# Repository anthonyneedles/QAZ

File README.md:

# **QAZ**

## Table of Contents

1. [Boards](#boards)
1. [About This Project](#about-this-project)
    1. [File Structure](#file-structure)
    1. [Dependencies](#dependencies)
1. [Programming](#programming)
1. [Software](#software)
1. [Building](#building)

## **Boards**

### [**QAZ 65%**](docs/guides/QAZ_65.md)

### [**QAZ Media**](docs/guides/QAZ_Media.md)

## **About This Project**

The QAZ project was created as a way for me to learn the USB protocol by writing a bare-metal USB
driver. Since a keyboard is a relatively simple USB device, and I like mechanical keyboards, I
decided that it would be a perfect project. The QAZ project is planned to support various different
keyboard layouts (only 65% and a Media board for now).

This repository holds files for both the software and hardware portions of this project. The
software consists of C++ source and header files, built using Make. Building is only supported
in Debian-based systems. CMSIS is used for some MCU hardware abstraction.

The PCB(s) for the different board versions have their schematic and layouts designed in KiCad,
which are contained in this library and can be manufactured in any generic fabrication house.

There is a maker space at my work that has a laser cutter that can cut acrylic, so decided to try
to keep costs down and make a "sandwich" case, which consists of several stacked layers of acrylic.

### **File Structure**

```
└── QAZ/
    ├── build/
    │   └── CMake build directory
    │
    ├── docs/
    │   │── guides/
    │   │   └── board-specific info, software info, etc.
    │   │
    │   ├── doxygen/
    │   │   └── Doxygen html output
    │   │
    │   └── media/
    │       └── diagrams, pictures, etc.
    │
    ├── hardware/
    │   ├── common/
    │   │   └── hardware utility used by both (e.g. KiCad libraries)
    │   │
    │   └── QAZ_*/
    │       └── PCB/case layer subdirectories for each QAZ configuration
    │
    ├── scripts/
    │   └── useful project scripts (cpplint.py, Doxyfile, etc.)
    │
    ├── src/
    │   └── all source files/module subdirectories, source-level CMakeLists.txt
    │
    └── LICENSE, README, top-level Makefile/CMakeLists.txt
```

The `docs\doxygen` and `build` directories are not tracked, and get made when the project is built.
The files in these directories are removed when the project is cleaned with `make clean`.

## **Programming**

The board programming guide can be found at [`docs/guides/Programming.md`](docs/guides/Programming.md).

## **Software**

The software guide can be found at [`docs/guides/Software.md`](docs/guides/Software.md).

## **Building**

The software building guide can be found at [`docs/guides/Building.md`](docs/guides/Building.md).

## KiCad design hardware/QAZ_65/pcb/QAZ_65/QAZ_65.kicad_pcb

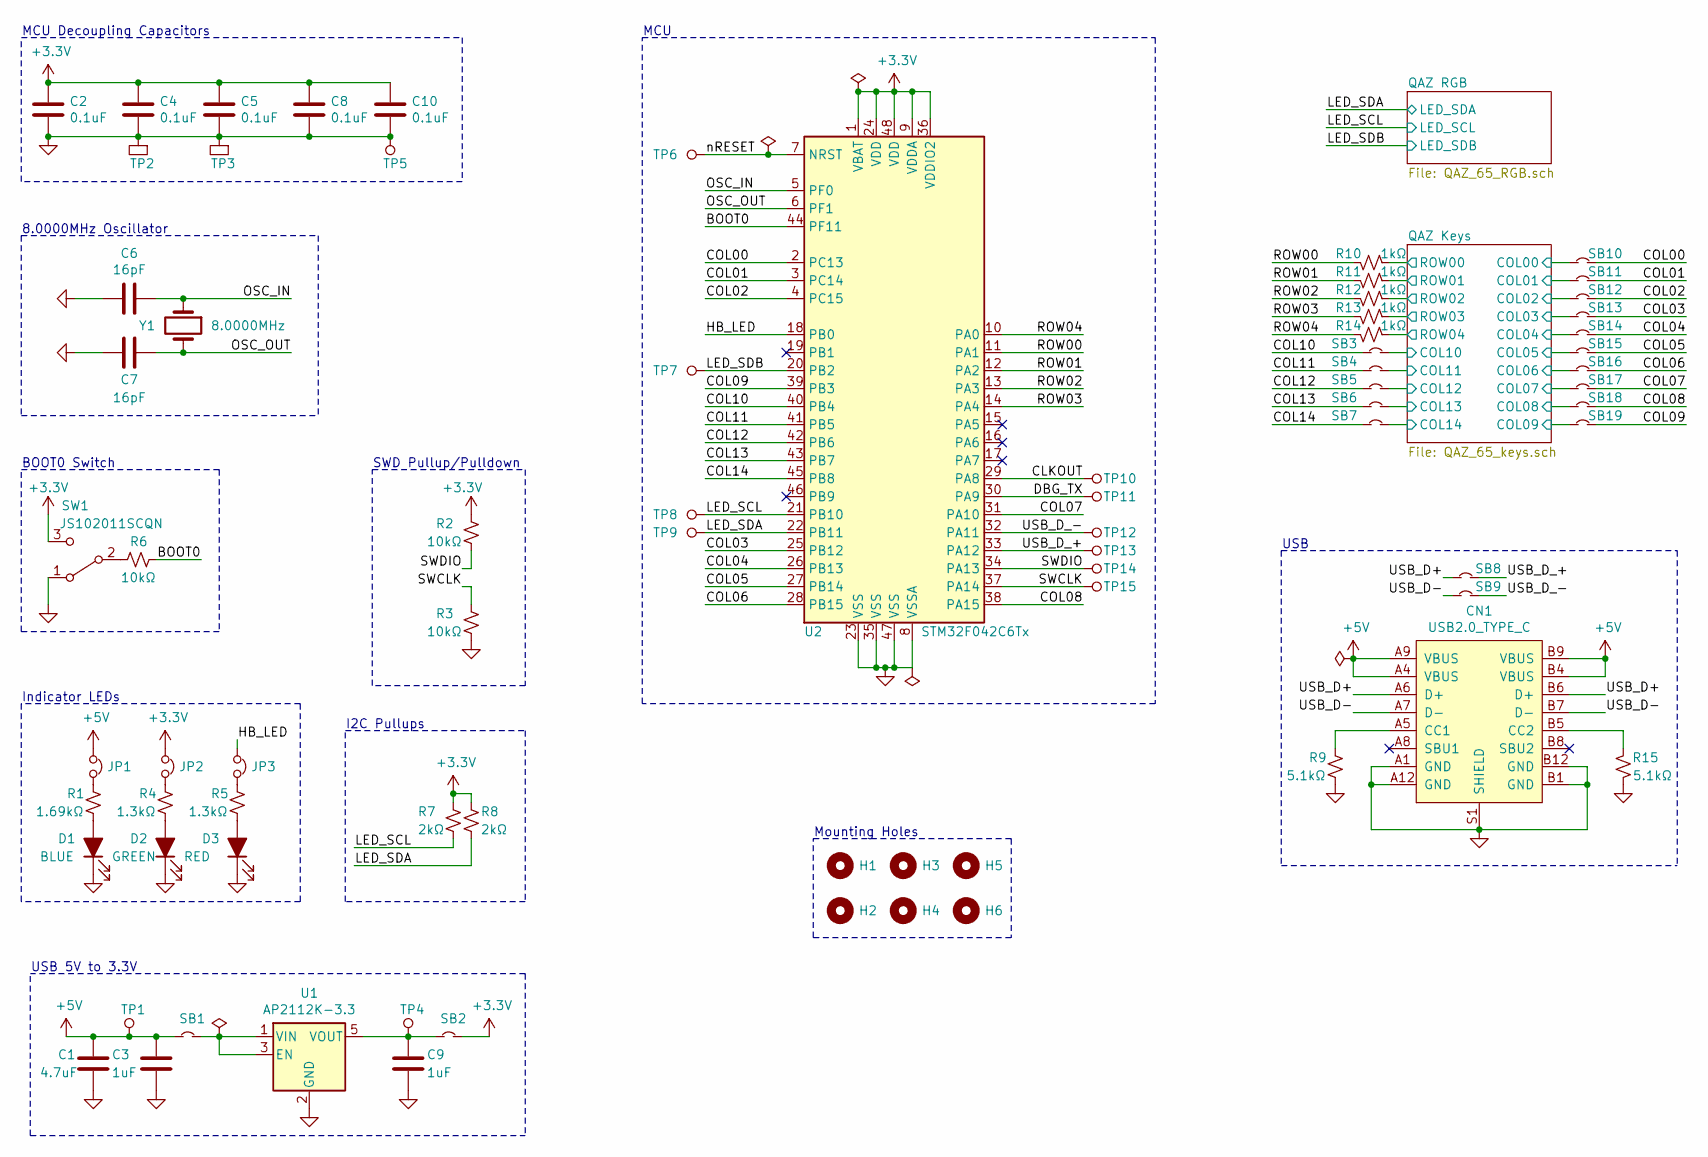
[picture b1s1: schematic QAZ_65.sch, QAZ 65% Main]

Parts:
C1: 4.7uF; C_0805_2012Metric_Pad1.15x1.40mm_HandSolder
C2, C4, C5, C8, C10: 0.1uF; C_0603_1608Metric_Pad1.05x0.95mm_HandSolder
C3, C9: 1uF; C_0603_1608Metric_Pad1.05x0.95mm_HandSolder
C6, C7: 16pF; C_0603_1608Metric_Pad1.05x0.95mm_HandSolder
CN1: USB2.0_TYPE_C; USB_C_GCT_USB4085
D1: BLUE; R_0603_1608Metric_Pad1.05x0.95mm_HandSolder
D2: GREEN; R_0603_1608Metric_Pad1.05x0.95mm_HandSolder
D3: RED; R_0603_1608Metric_Pad1.05x0.95mm_HandSolder
H1, H2, H3, H4, H5, H6: MountingHole; 4-40_NPTH
JP1, JP2, JP3: Jumper_NC_Small; PinHeader_1x02_P1.27mm_Vertical
R1: 1.69kΩ; R_0603_1608Metric_Pad1.05x0.95mm_HandSolder
R2, R3, R6: 10kΩ; R_0603_1608Metric_Pad1.05x0.95mm_HandSolder
R4, R5: 1.3kΩ; R_0603_1608Metric_Pad1.05x0.95mm_HandSolder
R7, R8: 2kΩ; R_0603_1608Metric_Pad1.05x0.95mm_HandSolder
R9, R15: 5.1kΩ; R_0603_1608Metric_Pad1.05x0.95mm_HandSolder
R10, R11, R12, R13, R14: 1kΩ; R_0603_1608Metric_Pad1.05x0.95mm_HandSolder
SB1, SB2, SB3, SB4, SB5, SB6, SB7, SB8, SB9, SB10, SB11, SB12, SB13, SB14, SB15, SB16, SB17, SB18, SB19: SolderBridge; R_0603_1608Metric_Pad1.05x0.95mm_HandSolder
SW1: JS102011SCQN; JS102011SCQN_SPDT
TP1, TP4, TP5, TP6, TP7, TP8, TP9, TP10, TP11, TP12, TP13, TP14, TP15: TestPoint; TestPoint_Thruhole_1.0mm
TP2, TP3: TestPoint_SMD_1812; TestPoint_SMD_1812_HS
U1: AP2112K-3.3; SOT-23-5
U2: STM32F042C6Tx; LQFP-48_7x7mm_P0.5mm
Y1: 8.0000MHz; Crystal_SMD_Abracon_ABM7-2Pin_6.0x3.5mm_HS

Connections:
+3V3: C2.2, C4.2, C5.2, C8.2, C10.2, JP2.1, R2.2, R7.2, R8.2, SB2.2, SW1.3 (C), U2.1 (VBAT), U2.9 (VDDA), U2.24 (VDD), U2.36 (VDDIO2), U2.48 (VDD); also elsewhere on the board
+5V: C1.2, C3.2, CN1.A4 (VBUS), CN1.A9 (VBUS), CN1.B4 (VBUS), CN1.B9 (VBUS), JP1.1, SB1.1, TP1.1; also elsewhere on the board
/BOOT0: R6.2, U2.44 (PF11)
/CLKOUT: TP10.1, U2.29 (PA8)
/COL00: SB10.2, U2.2 (PC13)
/COL01: SB11.2, U2.3 (PC14)
/COL02: SB12.2, U2.4 (PC15)
/COL03: SB13.2, U2.25 (PB12)
/COL04: SB14.2, U2.26 (PB13)
/COL05: SB15.2, U2.27 (PB14)
/COL06: SB16.2, U2.28 (PB15)
/COL07: SB17.2, U2.31 (PA10)
/COL08: SB18.2, U2.38 (PA15)
/COL09: SB19.2, U2.39 (PB3)
/COL10: SB3.1, U2.40 (PB4)
/COL11: SB4.1, U2.41 (PB5)
/COL12: SB5.1, U2.42 (PB6)
/COL13: SB6.1, U2.43 (PB7)
/COL14: SB7.1, U2.45 (PB8)
/DBG_TX: TP11.1, U2.30 (PA9)
/HB_LED: JP3.1, U2.18 (PB0)
/LED_SCL: R7.1, TP8.1, U2.21 (PB10); also elsewhere on the board
/LED_SDA: R8.1, TP9.1, U2.22 (PB11); also elsewhere on the board
/LED_SDB: TP7.1, U2.20 (PB2); also elsewhere on the board
/OSC_IN: C6.1, U2.5 (PF0), Y1.1
/OSC_OUT: C7.1, U2.6 (PF1), Y1.2
/QAZ Keys/COL00: SB10.1; also elsewhere on the board
/QAZ Keys/COL01: SB11.1; also elsewhere on the board
/QAZ Keys/COL02: SB12.1; also elsewhere on the board
/QAZ Keys/COL03: SB13.1; also elsewhere on the board
/QAZ Keys/COL04: SB14.1; also elsewhere on the board
/QAZ Keys/COL05: SB15.1; also elsewhere on the board
/QAZ Keys/COL06: SB16.1; also elsewhere on the board
/QAZ Keys/COL07: SB17.1; also elsewhere on the board
/QAZ Keys/COL08: SB18.1; also elsewhere on the board
/QAZ Keys/COL09: SB19.1; also elsewhere on the board
/QAZ Keys/COL10: SB3.2; also elsewhere on the board
/QAZ Keys/COL11: SB4.2; also elsewhere on the board
/QAZ Keys/COL12: SB5.2; also elsewhere on the board
/QAZ Keys/COL13: SB6.2; also elsewhere on the board
/QAZ Keys/COL14: SB7.2; also elsewhere on the board
/QAZ Keys/ROW00: R10.1; also elsewhere on the board
/QAZ Keys/ROW01: R11.1; also elsewhere on the board
/QAZ Keys/ROW02: R12.1; also elsewhere on the board
/QAZ Keys/ROW03: R13.1; also elsewhere on the board
/QAZ Keys/ROW04: R14.1; also elsewhere on the board
/ROW00: R10.2, U2.11 (PA1)
/ROW01: R11.2, U2.12 (PA2)
/ROW02: R12.2, U2.13 (PA3)
/ROW03: R13.2, U2.14 (PA4)
/ROW04: R14.2, U2.10 (PA0)
/SWCLK: R3.2, TP15.1, U2.37 (PA14)
/SWDIO: R2.1, TP14.1, U2.34 (PA13)
/USB_D+: CN1.A6 (D+), CN1.B6 (D+), SB8.1
/USB_D-: CN1.A7 (D-), CN1.B7 (D-), SB9.1
/USB_D_+: SB8.2, TP13.1, U2.33 (PA12)
/USB_D_-: SB9.2, TP12.1, U2.32 (PA11)
/nRESET: TP6.1, U2.7 (NRST)
GND: C1.1, C2.1, C3.1, C4.1, C5.1, C6.2, C7.2, C8.1, C9.1, C10.1, CN1.A1 (GND), CN1.A12 (GND), CN1.B1 (GND), CN1.B12 (GND), CN1.S1 (SHIELD), D1.1 (K), D2.1 (K), D3.1 (K), R3.1, R9.1, R15.1, SW1.1 (A), TP2.1, TP3.1, TP5.1, U1.2 (GND), U2.8 (VSSA), U2.23 (VSS), U2.35 (VSS), U2.47 (VSS); also elsewhere on the board
unnamed: C9.2, SB2.1, TP4.1, U1.5 (VOUT)
unnamed: CN1.A5 (CC1), R9.2
unnamed: CN1.B5 (CC2), R15.2
unnamed: D1.2 (A), R1.1
unnamed: D2.2 (A), R4.1
unnamed: D3.2 (A), R5.1
unnamed: JP1.2, R1.2
unnamed: JP2.2, R4.2
unnamed: JP3.2, R5.2
unnamed: R6.1, SW1.2 (B)
unnamed: SB1.2, U1.1 (VIN), U1.3 (EN)

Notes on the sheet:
USB 5V to 3.3V
MCU Decoupling Capacitors
8.0000MHz Oscillator
BOOT0 Switch
Indicator LEDs
I2C Pullups
MCU
SWD Pullup/Pulldown
USB
Mounting Holes

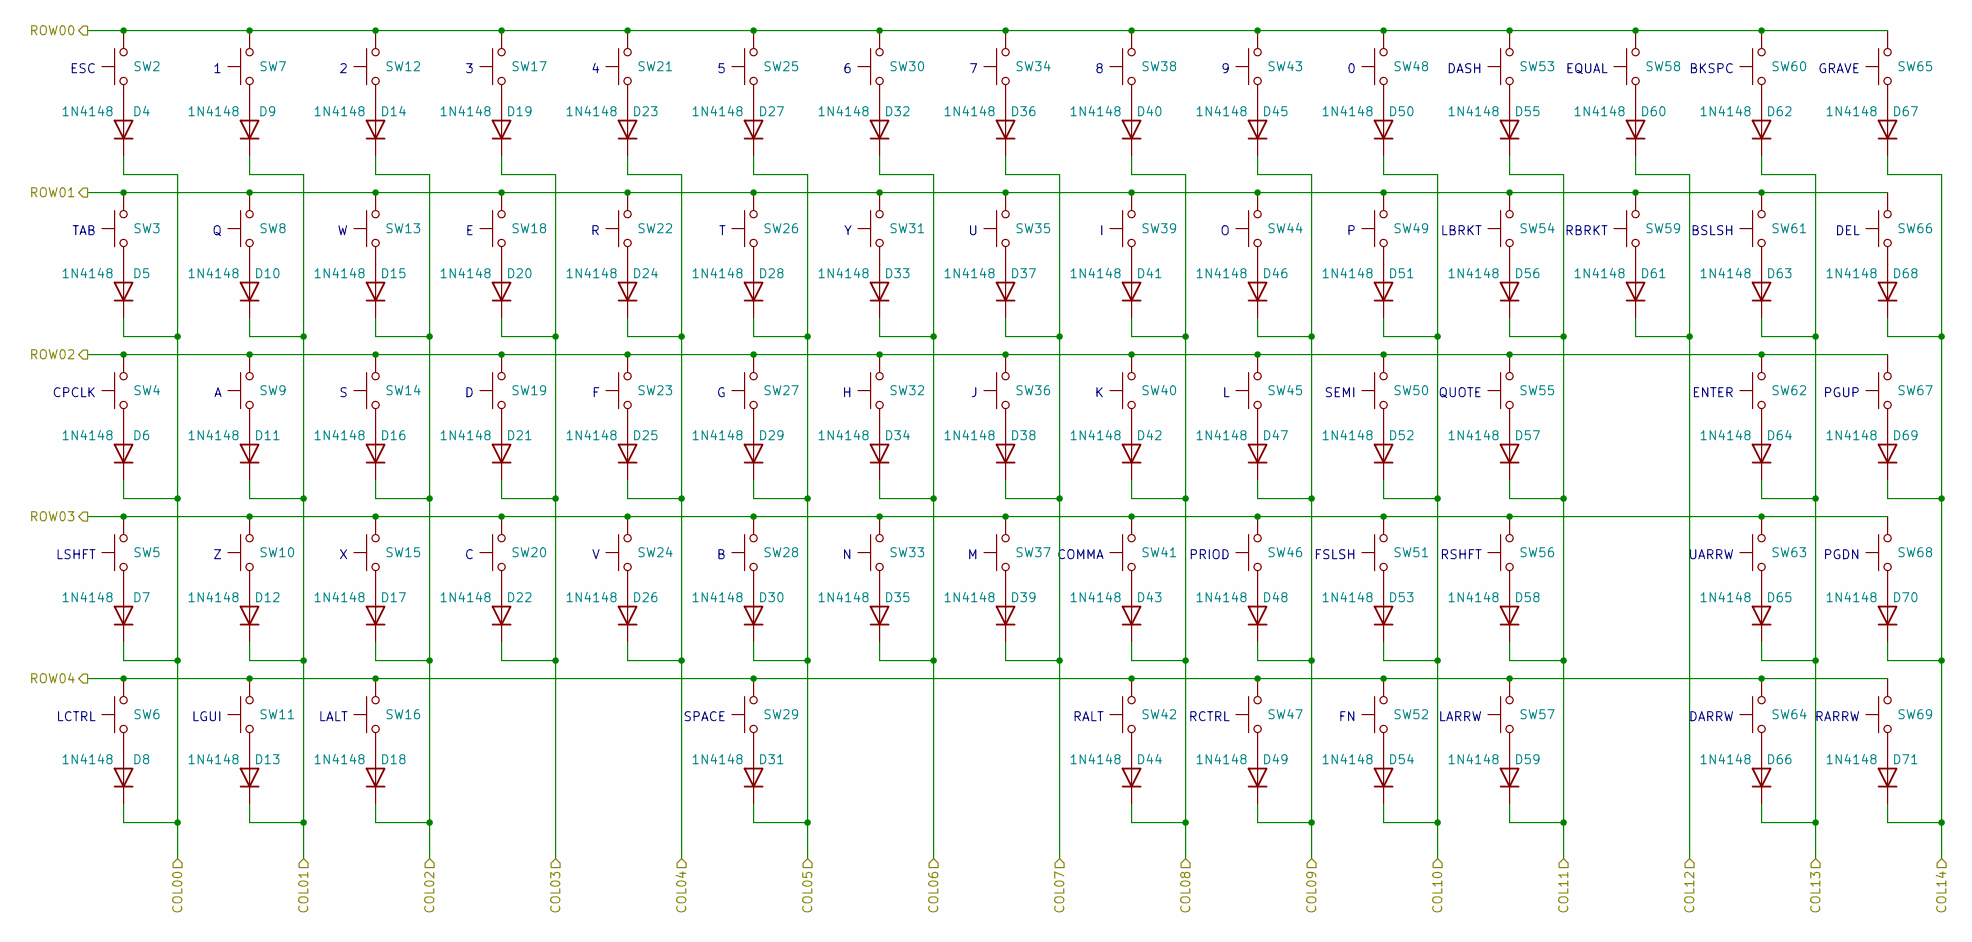
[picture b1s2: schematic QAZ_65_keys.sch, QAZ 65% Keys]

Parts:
D4, D5, D6, D7, D8, D9, D10, D11, D12, D13, D14, D15, D16, D17, D18, D19, D20, D21, D22, D23, D24, D25, D26, D27, D28, D29, D30, D31, D32, D33, D34, D35, D36, D37, D38, D39, D40, D41, D42, D43, D44, D45, D46, D47, D48, D49, D50, D51, D52, D53, D54, D55, D56, D57, D58, D59, D60, D61, D62, D63, D64, D65, D66, D67, D68, D69, D70, D71: 1N4148; D_DO-35_SOD27_P7.62mm_Horizontal
SW2, SW7, SW8, SW9, SW10, SW12, SW13, SW14, SW15, SW17, SW18, SW19, SW20, SW21, SW22, SW23, SW24, SW25, SW26, SW27, SW28, SW30, SW31, SW32, SW33, SW34, SW35, SW36, SW37, SW38, SW39, SW40, SW41, SW42, SW43, SW44, SW45, SW46, SW47, SW48, SW49, SW50, SW51, SW52, SW53, SW54, SW55, SW57, SW58, SW59, SW63, SW64, SW65, SW66, SW67, SW68, SW69: Cherry MX; SW_Cherry_MX_1.00u_PCB
SW3, SW61: Cherry MX; SW_Cherry_MX_1.50u_PCB
SW4, SW56: Cherry MX; SW_Cherry_MX_1.75u_PCB
SW5, SW62: Cherry MX; SW_Cherry_MX_2.25u_PCB
SW6, SW11, SW16: Cherry MX; SW_Cherry_MX_1.25u_PCB
SW29: Cherry MX; SW_Cherry_MX_6.25u_PCB
SW60: Cherry MX; SW_Cherry_MX_2.00u_PCB

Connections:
/QAZ Keys/COL00: D4.1 (K), D5.1 (K), D6.1 (K), D7.1 (K), D8.1 (K); also elsewhere on the board
/QAZ Keys/COL01: D9.1 (K), D10.1 (K), D11.1 (K), D12.1 (K), D13.1 (K); also elsewhere on the board
/QAZ Keys/COL02: D14.1 (K), D15.1 (K), D16.1 (K), D17.1 (K), D18.1 (K); also elsewhere on the board
/QAZ Keys/COL03: D19.1 (K), D20.1 (K), D21.1 (K), D22.1 (K); also elsewhere on the board
/QAZ Keys/COL04: D23.1 (K), D24.1 (K), D25.1 (K), D26.1 (K); also elsewhere on the board
/QAZ Keys/COL05: D27.1 (K), D28.1 (K), D29.1 (K), D30.1 (K), D31.1 (K); also elsewhere on the board
/QAZ Keys/COL06: D32.1 (K), D33.1 (K), D34.1 (K), D35.1 (K); also elsewhere on the board
/QAZ Keys/COL07: D36.1 (K), D37.1 (K), D38.1 (K), D39.1 (K); also elsewhere on the board
/QAZ Keys/COL08: D40.1 (K), D41.1 (K), D42.1 (K), D43.1 (K), D44.1 (K); also elsewhere on the board
/QAZ Keys/COL09: D45.1 (K), D46.1 (K), D47.1 (K), D48.1 (K), D49.1 (K); also elsewhere on the board
/QAZ Keys/COL10: D50.1 (K), D51.1 (K), D52.1 (K), D53.1 (K), D54.1 (K); also elsewhere on the board
/QAZ Keys/COL11: D55.1 (K), D56.1 (K), D57.1 (K), D58.1 (K), D59.1 (K); also elsewhere on the board
/QAZ Keys/COL12: D60.1 (K), D61.1 (K); also elsewhere on the board
/QAZ Keys/COL13: D62.1 (K), D63.1 (K), D64.1 (K), D65.1 (K), D66.1 (K); also elsewhere on the board
/QAZ Keys/COL14: D67.1 (K), D68.1 (K), D69.1 (K), D70.1 (K), D71.1 (K); also elsewhere on the board
/QAZ Keys/ROW00: SW2.2, SW7.2, SW12.2, SW17.2, SW21.2, SW25.2, SW30.2, SW34.2, SW38.2, SW43.2, SW48.2, SW53.2, SW58.2, SW60.2, SW65.2; also elsewhere on the board
/QAZ Keys/ROW01: SW3.2, SW8.2, SW13.2, SW18.2, SW22.2, SW26.2, SW31.2, SW35.2, SW39.2, SW44.2, SW49.2, SW54.2, SW59.2, SW61.2, SW66.2; also elsewhere on the board
/QAZ Keys/ROW02: SW4.2, SW9.2, SW14.2, SW19.2, SW23.2, SW27.2, SW32.2, SW36.2, SW40.2, SW45.2, SW50.2, SW55.2, SW62.2, SW67.2; also elsewhere on the board
/QAZ Keys/ROW03: SW5.2, SW10.2, SW15.2, SW20.2, SW24.2, SW28.2, SW33.2, SW37.2, SW41.2, SW46.2, SW51.2, SW56.2, SW63.2, SW68.2; also elsewhere on the board
/QAZ Keys/ROW04: SW6.2, SW11.2, SW16.2, SW29.2, SW42.2, SW47.2, SW52.2, SW57.2, SW64.2, SW69.2; also elsewhere on the board
unnamed: D4.2 (A), SW2.1
unnamed: D5.2 (A), SW3.1
unnamed: D6.2 (A), SW4.1
unnamed: D7.2 (A), SW5.1
unnamed: D8.2 (A), SW6.1
unnamed: D9.2 (A), SW7.1
unnamed: D10.2 (A), SW8.1
unnamed: D11.2 (A), SW9.1
unnamed: D12.2 (A), SW10.1
unnamed: D13.2 (A), SW11.1
unnamed: D14.2 (A), SW12.1
unnamed: D15.2 (A), SW13.1
unnamed: D16.2 (A), SW14.1
unnamed: D17.2 (A), SW15.1
unnamed: D18.2 (A), SW16.1
unnamed: D19.2 (A), SW17.1
unnamed: D20.2 (A), SW18.1
unnamed: D21.2 (A), SW19.1
unnamed: D22.2 (A), SW20.1
unnamed: D23.2 (A), SW21.1
unnamed: D24.2 (A), SW22.1
unnamed: D25.2 (A), SW23.1
unnamed: D26.2 (A), SW24.1
unnamed: D27.2 (A), SW25.1
unnamed: D28.2 (A), SW26.1
unnamed: D29.2 (A), SW27.1
unnamed: D30.2 (A), SW28.1
unnamed: D31.2 (A), SW29.1
unnamed: D32.2 (A), SW30.1
unnamed: D33.2 (A), SW31.1
unnamed: D34.2 (A), SW32.1
unnamed: D35.2 (A), SW33.1
unnamed: D36.2 (A), SW34.1
unnamed: D37.2 (A), SW35.1
unnamed: D38.2 (A), SW36.1
unnamed: D39.2 (A), SW37.1
unnamed: D40.2 (A), SW38.1
unnamed: D41.2 (A), SW39.1
unnamed: D42.2 (A), SW40.1
unnamed: D43.2 (A), SW41.1
unnamed: D44.2 (A), SW42.1
unnamed: D45.2 (A), SW43.1
unnamed: D46.2 (A), SW44.1
unnamed: D47.2 (A), SW45.1
unnamed: D48.2 (A), SW46.1
unnamed: D49.2 (A), SW47.1
unnamed: D50.2 (A), SW48.1
unnamed: D51.2 (A), SW49.1
unnamed: D52.2 (A), SW50.1
unnamed: D53.2 (A), SW51.1
unnamed: D54.2 (A), SW52.1
unnamed: D55.2 (A), SW53.1
unnamed: D56.2 (A), SW54.1
unnamed: D57.2 (A), SW55.1
unnamed: D58.2 (A), SW56.1
unnamed: D59.2 (A), SW57.1
unnamed: D60.2 (A), SW58.1
unnamed: D61.2 (A), SW59.1
unnamed: D62.2 (A), SW60.1
unnamed: D63.2 (A), SW61.1
unnamed: D64.2 (A), SW62.1
unnamed: D65.2 (A), SW63.1
unnamed: D66.2 (A), SW64.1
unnamed: D67.2 (A), SW65.1
unnamed: D68.2 (A), SW66.1
unnamed: D69.2 (A), SW67.1
unnamed: D70.2 (A), SW68.1
unnamed: D71.2 (A), SW69.1

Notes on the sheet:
LCTRL
ESC
TAB
CPCLK
LSHFT
DASH
EQUAL
BKSPC
GRAVE
LGUI
LALT
LBRKT
RBRKT
BSLSH
DEL
SEMI
QUOTE
ENTER
PGUP
COMMA
PRIOD
FSLSH
RCTRL
RSHFT
SPACE
RALT
LARRW
PGDN
RARRW
DARRW
UARRW

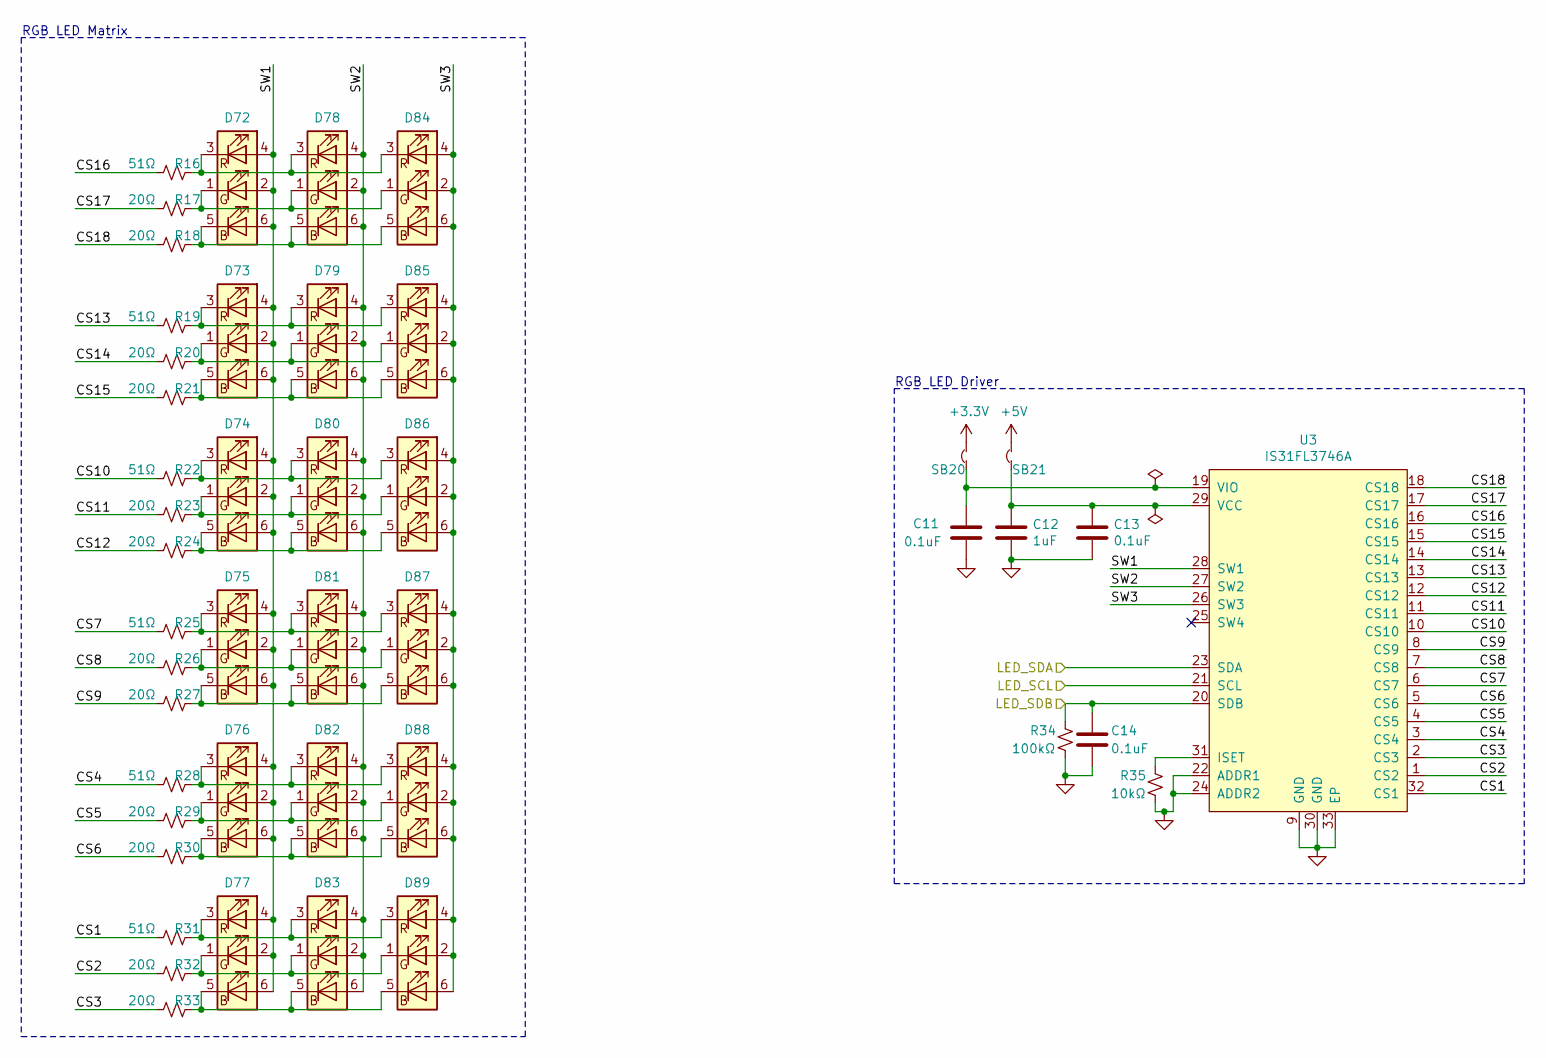
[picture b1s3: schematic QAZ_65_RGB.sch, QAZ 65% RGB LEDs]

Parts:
C11, C13, C14: 0.1uF; C_0603_1608Metric_Pad1.05x0.95mm_HandSolder
C12: 1uF; C_0603_1608Metric_Pad1.05x0.95mm_HandSolder
D72, D73, D74, D75, D76, D77, D78, D79, D80, D81, D82, D83, D84, D85, D86, D87, D88, D89: 19-337C_RSBHGHC-A88_4T; 0606_1616Metric_HS
R16, R19, R22, R25, R28, R31: 51Ω; R_0603_1608Metric_Pad1.05x0.95mm_HandSolder
R17, R18, R20, R21, R23, R24, R26, R27, R29, R30, R32, R33: 20Ω; R_0603_1608Metric_Pad1.05x0.95mm_HandSolder
R34: 100kΩ; R_0603_1608Metric_Pad1.05x0.95mm_HandSolder
R35: 10kΩ; R_0603_1608Metric_Pad1.05x0.95mm_HandSolder
SB20, SB21: SolderBridge; R_0603_1608Metric_Pad1.05x0.95mm_HandSolder
U3: IS31FL3746A; QFN-32-1EP_4x4mm_P0.4mm_EP2.9x2.9mm_HS

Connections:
+3V3: SB20.2; also elsewhere on the board
+5V: SB21.2; also elsewhere on the board
/LED_SCL: U3.21 (SCL); also elsewhere on the board
/LED_SDA: U3.23 (SDA); also elsewhere on the board
/LED_SDB: C14.2, R34.2, U3.20 (SDB); also elsewhere on the board
/QAZ RGB/CS1: R31.2, U3.32 (CS1)
/QAZ RGB/CS2: R32.2, U3.1 (CS2)
/QAZ RGB/CS3: R33.2, U3.2 (CS3)
/QAZ RGB/CS4: R28.2, U3.3 (CS4)
/QAZ RGB/CS5: R29.2, U3.4 (CS5)
/QAZ RGB/CS6: R30.2, U3.5 (CS6)
/QAZ RGB/CS7: R25.2, U3.6 (CS7)
/QAZ RGB/CS8: R26.2, U3.7 (CS8)
/QAZ RGB/CS9: R27.2, U3.8 (CS9)
/QAZ RGB/CS10: R22.2, U3.10 (CS10)
/QAZ RGB/CS11: R23.2, U3.11 (CS11)
/QAZ RGB/CS12: R24.2, U3.12 (CS12)
/QAZ RGB/CS13: R19.2, U3.13 (CS13)
/QAZ RGB/CS14: R20.2, U3.14 (CS14)
/QAZ RGB/CS15: R21.2, U3.15 (CS15)
/QAZ RGB/CS16: R16.2, U3.16 (CS16)
/QAZ RGB/CS17: R17.2, U3.17 (CS17)
/QAZ RGB/CS18: R18.2, U3.18 (CS18)
/QAZ RGB/SW1: D72.2, D72.4, D72.6, D73.2, D73.4, D73.6, D74.2, D74.4, D74.6, D75.2, D75.4, D75.6, D76.2, D76.4, D76.6, D77.2, D77.4, D77.6, U3.28 (SW1)
/QAZ RGB/SW2: D78.2, D78.4, D78.6, D79.2, D79.4, D79.6, D80.2, D80.4, D80.6, D81.2, D81.4, D81.6, D82.2, D82.4, D82.6, D83.2, D83.4, D83.6, U3.27 (SW2)
/QAZ RGB/SW3: D84.2, D84.4, D84.6, D85.2, D85.4, D85.6, D86.2, D86.4, D86.6, D87.2, D87.4, D87.6, D88.2, D88.4, D88.6, D89.2, D89.4, D89.6, U3.26 (SW3)
GND: C11.1, C12.1, C13.1, C14.1, R34.1, R35.1, U3.9 (GND), U3.22 (ADDR1), U3.24 (ADDR2), U3.30 (GND), U3.33 (EP); also elsewhere on the board
unnamed: C11.2, SB20.1, U3.19 (VIO)
unnamed: C12.2, C13.2, SB21.1, U3.29 (VCC)
unnamed: D72.1, D78.1, D84.1, R17.1
unnamed: D72.3, D78.3, D84.3, R16.1
unnamed: D72.5, D78.5, D84.5, R18.1
unnamed: D73.1, D79.1, D85.1, R20.1
unnamed: D73.3, D79.3, D85.3, R19.1
unnamed: D73.5, D79.5, D85.5, R21.1
unnamed: D74.1, D80.1, D86.1, R23.1
unnamed: D74.3, D80.3, D86.3, R22.1
unnamed: D74.5, D80.5, D86.5, R24.1
unnamed: D75.1, D81.1, D87.1, R26.1
unnamed: D75.3, D81.3, D87.3, R25.1
unnamed: D75.5, D81.5, D87.5, R27.1
unnamed: D76.1, D82.1, D88.1, R29.1
unnamed: D76.3, D82.3, D88.3, R28.1
unnamed: D76.5, D82.5, D88.5, R30.1
unnamed: D77.1, D83.1, D89.1, R32.1
unnamed: D77.3, D83.3, D89.3, R31.1
unnamed: D77.5, D83.5, D89.5, R33.1
unnamed: R35.2, U3.31 (ISET)

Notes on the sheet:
RGB LED Driver
RGB LED Matrix

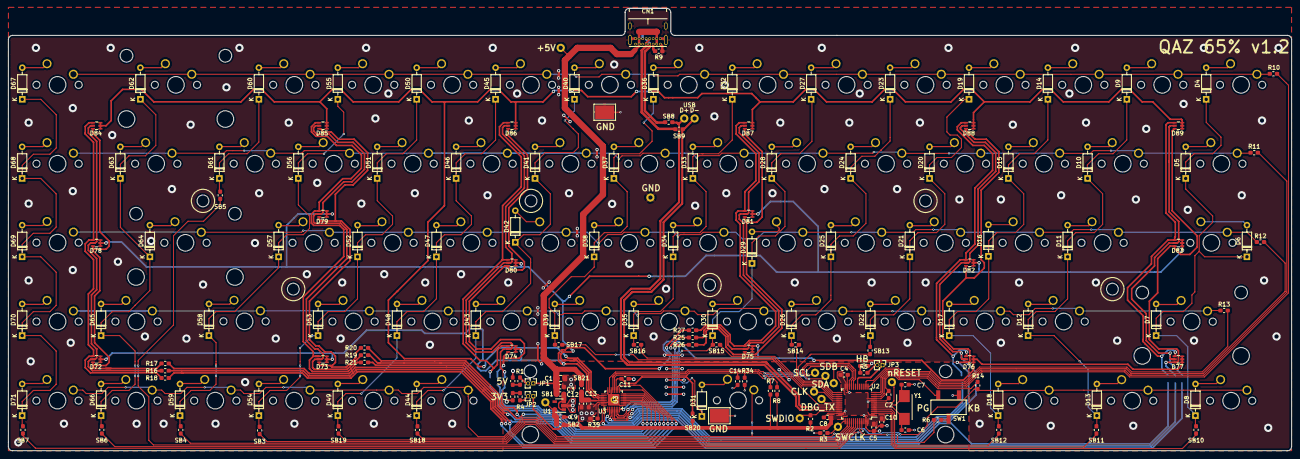
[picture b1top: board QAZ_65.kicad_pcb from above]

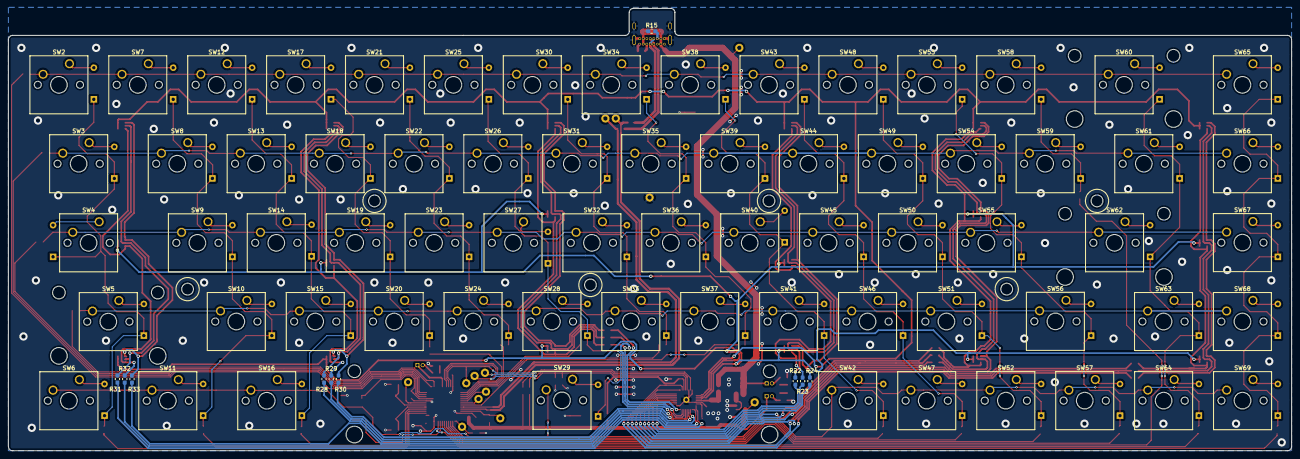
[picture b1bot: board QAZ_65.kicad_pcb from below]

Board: 2 copper layers, 309.0 x 106.5 mm, 257 parts (78 on the bottom side), 180 nets.

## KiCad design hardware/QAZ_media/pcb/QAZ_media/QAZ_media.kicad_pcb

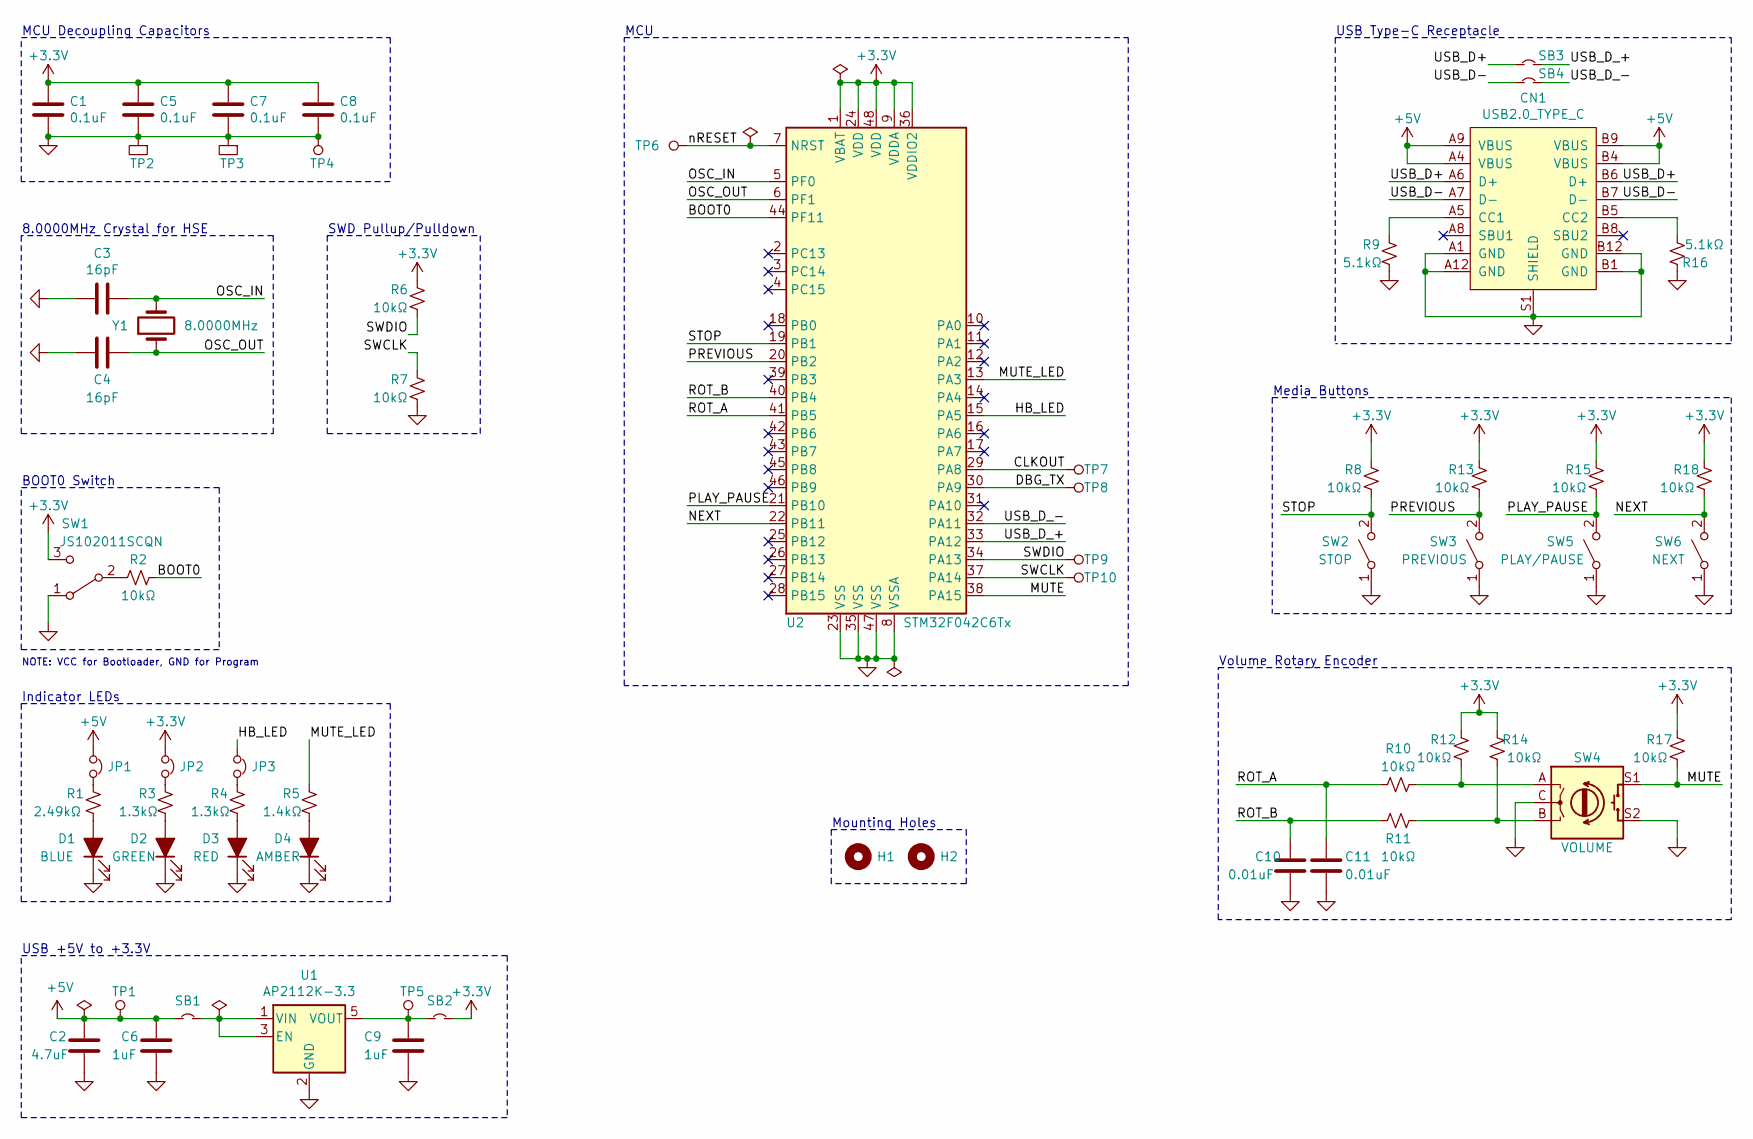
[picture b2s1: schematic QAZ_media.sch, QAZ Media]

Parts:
C1, C5, C7, C8: 0.1uF; C_0603_1608Metric_Pad1.05x0.95mm_HandSolder
C2: 4.7uF; C_0805_2012Metric_Pad1.15x1.40mm_HandSolder
C3, C4: 16pF; C_0603_1608Metric_Pad1.05x0.95mm_HandSolder
C6, C9: 1uF; C_0603_1608Metric_Pad1.05x0.95mm_HandSolder
C10, C11: 0.01uF; C_0603_1608Metric_Pad1.05x0.95mm_HandSolder
CN1: USB2.0_TYPE_C; USB_C_GCT_USB4085
D1: BLUE; R_0603_1608Metric_Pad1.05x0.95mm_HandSolder
D2: GREEN; R_0603_1608Metric_Pad1.05x0.95mm_HandSolder
D3: RED; R_0603_1608Metric_Pad1.05x0.95mm_HandSolder
D4: AMBER; PinHeader_1x02_P2.54mm_Vertical
H1, H2: MountingHole; 4-40_NPTH
JP1, JP2, JP3: Jumper_NC_Small; PinHeader_1x02_P1.27mm_Vertical
R1: 2.49kΩ; R_0603_1608Metric_Pad1.05x0.95mm_HandSolder
R2, R6, R7, R8, R10, R11, R12, R13, R14, R15, R17, R18: 10kΩ; R_0603_1608Metric_Pad1.05x0.95mm_HandSolder
R3, R4: 1.3kΩ; R_0603_1608Metric_Pad1.05x0.95mm_HandSolder
R5: 1.4kΩ; R_0603_1608Metric_Pad1.05x0.95mm_HandSolder
R9, R16: 5.1kΩ; R_0603_1608Metric_Pad1.05x0.95mm_HandSolder
SB1, SB2, SB3, SB4: SolderBridge; R_0603_1608Metric_Pad1.05x0.95mm_HandSolder
SW1: JS102011SCQN; JS102011SCQN_SPDT
SW2: STOP; NCA2
SW3: PREVIOUS; NCA2
SW4: VOLUME; RotaryEncoder_Alps_EC11E-Switch_Vertical_H20mm
SW5: PLAY/PAUSE; NCA2
SW6: NEXT; NCA2
TP1, TP4, TP5, TP6, TP7, TP8, TP9, TP10: TestPoint_Thruhole_0.7mm
TP2, TP3: TestPoint_SMD_1812; TestPoint_SMD_1812_HS
U1: AP2112K-3.3; SOT-23-5
U2: STM32F042C6Tx; LQFP-48_7x7mm_P0.5mm
Y1: 8.0000MHz; Crystal_SMD_Abracon_ABM7-2Pin_6.0x3.5mm_HS

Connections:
+3V3: C1.1, C5.1, C7.1, C8.1, JP2.1, R6.1, R8.1, R12.1, R13.1, R14.1, R15.1, R17.1, R18.1, SB2.2, SW1.3 (C), U2.1 (VBAT), U2.9 (VDDA), U2.24 (VDD), U2.36 (VDDIO2), U2.48 (VDD)
+5V: C2.1, C6.1, CN1.A4 (VBUS), CN1.A9 (VBUS), CN1.B4 (VBUS), CN1.B9 (VBUS), JP1.1, SB1.1, TP1.1
/BOOT0: R2.1, U2.44 (PF11)
/CLKOUT: TP7.1, U2.29 (PA8)
/DBG_TX: TP8.1, U2.30 (PA9)
/HB_LED: JP3.1, U2.15 (PA5)
/MUTE: R17.2, SW4.S1, U2.38 (PA15)
/MUTE_LED: R5.1, U2.13 (PA3)
/NEXT: R18.2, SW6.2 (B), U2.22 (PB11)
/OSC_IN: C3.1, U2.5 (PF0), Y1.2
/OSC_OUT: C4.1, U2.6 (PF1), Y1.1
/PLAY_PAUSE: R15.2, SW5.2 (B), U2.21 (PB10)
/PREVIOUS: R13.2, SW3.2 (B), U2.20 (PB2)
/ROT_A: C11.1, R10.1, U2.41 (PB5)
/ROT_B: C10.1, R11.1, U2.40 (PB4)
/STOP: R8.2, SW2.2 (B), U2.19 (PB1)
/SWCLK: R7.1, TP10.1, U2.37 (PA14)
/SWDIO: R6.2, TP9.1, U2.34 (PA13)
/USB_D+: CN1.A6 (D+), CN1.B6 (D+), SB3.1
/USB_D-: CN1.A7 (D-), CN1.B7 (D-), SB4.1
/USB_D_+: SB3.2, U2.33 (PA12)
/USB_D_-: SB4.2, U2.32 (PA11)
/nRESET: TP6.1, U2.7 (NRST)
GND: C1.2, C2.2, C3.2, C4.2, C5.2, C6.2, C7.2, C8.2, C9.2, C10.2, C11.2, CN1.A1 (GND), CN1.A12 (GND), CN1.B1 (GND), CN1.B12 (GND), CN1.S1 (SHIELD), D1.1 (K), D2.1 (K), D3.1 (K), D4.1 (K), R7.2, R9.2, R16.1, SW1.1 (A), SW2.1 (A), SW3.1 (A), SW4.C, SW4.S2, SW5.1 (A), SW6.1 (A), TP2.1, TP3.1, TP4.1, U1.2 (GND), U2.8 (VSSA), U2.23 (VSS), U2.35 (VSS), U2.47 (VSS)
unnamed: C9.1, SB2.1, TP5.1, U1.5 (VOUT)
unnamed: CN1.A5 (CC1), R9.1
unnamed: CN1.B5 (CC2), R16.2
unnamed: D1.2 (A), R1.2
unnamed: D2.2 (A), R3.2
unnamed: D3.2 (A), R4.2
unnamed: D4.2 (A), R5.2
unnamed: JP1.2, R1.1
unnamed: JP2.2, R3.1
unnamed: JP3.2, R4.1
unnamed: R2.2, SW1.2 (B)
unnamed: R10.2, R12.2, SW4.A
unnamed: R11.2, R14.2, SW4.B
unnamed: SB1.2, U1.1 (VIN), U1.3 (EN)

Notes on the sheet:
MCU Decoupling Capacitors
8.0000MHz Crystal for HSE
BOOT0 Switch
NOTE: VCC for Bootloader, GND for Program
Indicator LEDs
USB +5V to +3.3V
SWD Pullup/Pulldown
MCU
USB Type-C Receptacle
Media Buttons
Volume Rotary Encoder
Mounting Holes

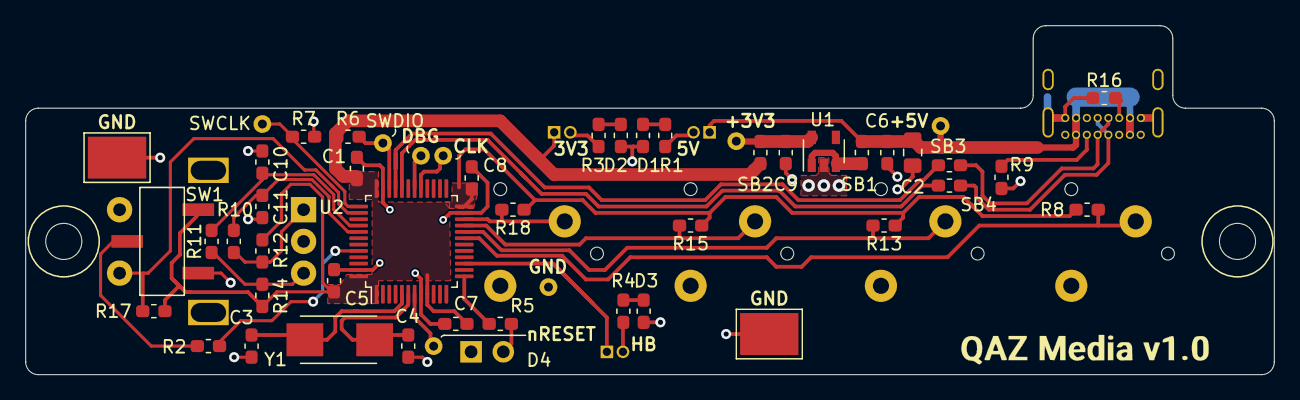
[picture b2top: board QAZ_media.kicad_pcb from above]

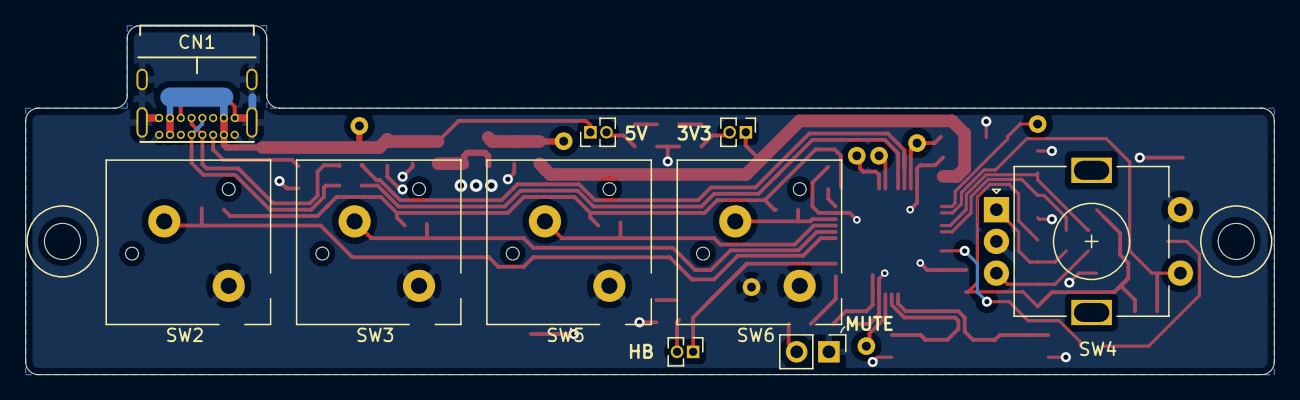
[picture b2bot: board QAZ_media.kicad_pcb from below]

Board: 2 copper layers, 98.4 x 27.5 mm, 62 parts (10 on the bottom side), 38 nets.

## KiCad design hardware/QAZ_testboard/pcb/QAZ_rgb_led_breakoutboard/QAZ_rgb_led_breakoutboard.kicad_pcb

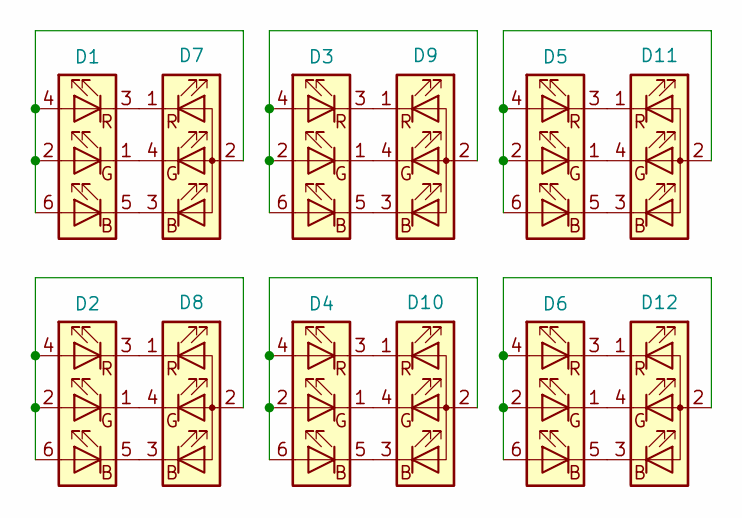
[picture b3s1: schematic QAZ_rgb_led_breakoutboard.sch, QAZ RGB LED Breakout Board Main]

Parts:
D1, D2, D3, D4, D5, D6: 19-337C_RSBHGHC-A88_4T; 0606_1616Metric_HS
D7, D8, D9, D10, D11, D12: LED_RABG; LED_D5.0mm-4_RGB

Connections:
unnamed: D1.1, D7.4 (GK)
unnamed: D1.2, D1.4, D1.6, D7.2 (A)
unnamed: D1.3, D7.1 (RK)
unnamed: D1.5, D7.3 (BK)
unnamed: D2.1, D8.4 (GK)
unnamed: D2.2, D2.4, D2.6, D8.2 (A)
unnamed: D2.3, D8.1 (RK)
unnamed: D2.5, D8.3 (BK)
unnamed: D3.1, D9.4 (GK)
unnamed: D3.2, D3.4, D3.6, D9.2 (A)
unnamed: D3.3, D9.1 (RK)
unnamed: D3.5, D9.3 (BK)
unnamed: D4.3, D10.1 (RK)
unnamed: D4.2, D4.4, D4.6, D10.2 (A)
unnamed: D4.5, D10.3 (BK)
unnamed: D4.1, D10.4 (GK)
unnamed: D5.3, D11.1 (RK)
unnamed: D5.2, D5.4, D5.6, D11.2 (A)
unnamed: D5.5, D11.3 (BK)
unnamed: D5.1, D11.4 (GK)
unnamed: D6.3, D12.1 (RK)
unnamed: D6.2, D6.4, D6.6, D12.2 (A)
unnamed: D6.5, D12.3 (BK)
unnamed: D6.1, D12.4 (GK)

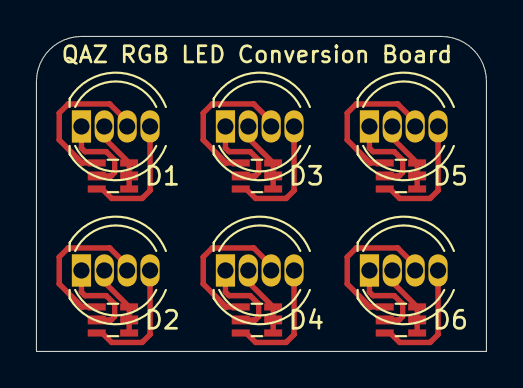
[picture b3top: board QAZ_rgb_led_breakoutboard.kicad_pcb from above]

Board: 2 copper layers, 25.0 x 17.5 mm, 12 parts (0 on the bottom side), 24 nets.
